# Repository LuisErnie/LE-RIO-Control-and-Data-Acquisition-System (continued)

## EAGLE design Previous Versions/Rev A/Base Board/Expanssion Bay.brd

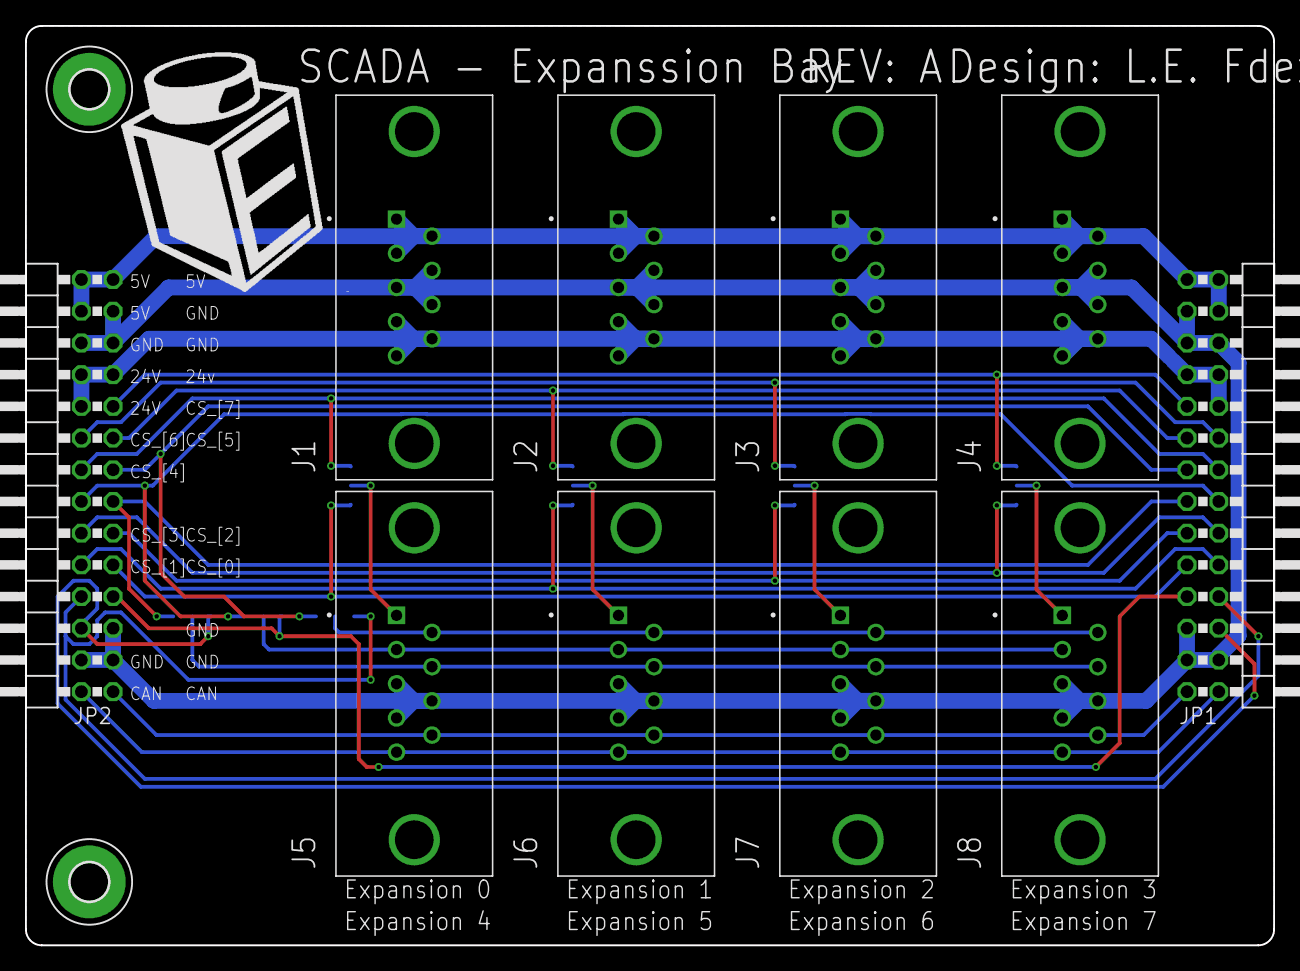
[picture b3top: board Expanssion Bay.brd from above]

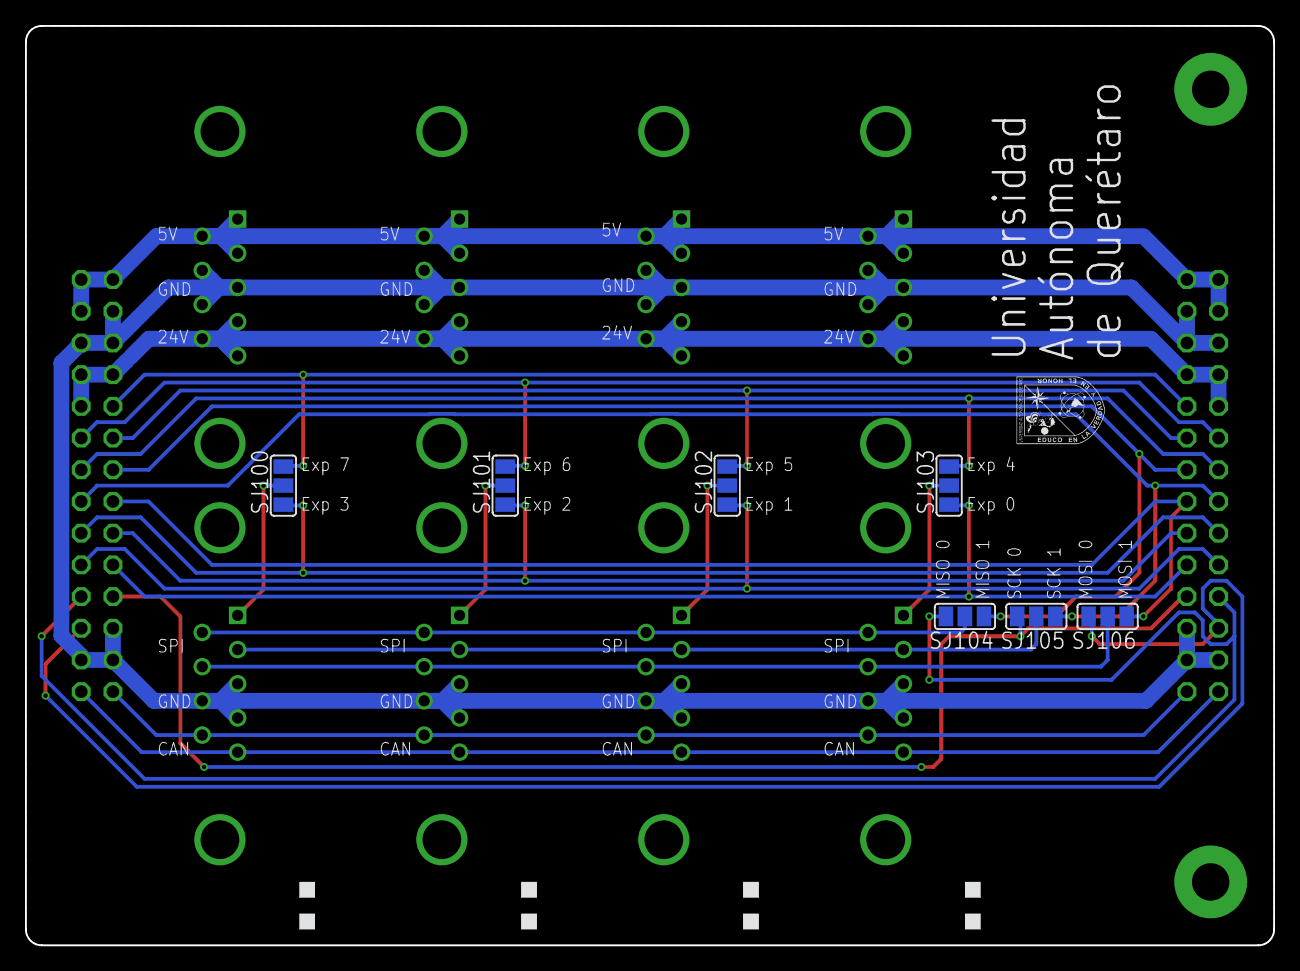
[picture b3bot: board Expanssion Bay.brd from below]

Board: 2 copper layers, 100.0 x 73.7 mm, 19 parts (7 on the bottom side), 26 nets.

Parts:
H1, H2: MOUNT-PAD-ROUND3.0; 3,0-PAD
J1, J2, J3, J4, J5, J6, J7, J8: LD09S24A4GV00LF
JP1, JP2: 2X14/90
SJ100, SJ101, SJ102, SJ103, SJ104, SJ105, SJ106: SJ_2

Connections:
+24V: J1.4, J1.5, J1.9, J2.4, J2.5, J2.9, J3.4, J3.5, J3.9, J4.4, J4.5, J4.9, JP1.7, JP1.8, JP1.10, JP2.20, JP2.21, JP2.22
AGND: J1.3, J1.7, J1.8, J2.3, J2.7, J2.8, J3.3, J3.7, J3.8, J4.3, J4.7, J4.8, J5.3, J5.4, J5.8, J6.3, J6.4, J6.8, J7.3, J7.4, J7.8, J8.3, J8.4, J8.8, JP1.3, JP1.5, JP1.6, JP1.23, JP1.25, JP1.26, JP2.3, JP2.4, JP2.5, JP2.23, JP2.24, JP2.25
CAN_H: J5.5, J6.5, J7.5, J8.5, JP1.28, JP2.2
CAN_L: J5.9, J6.9, J7.9, J8.9, JP1.27, JP2.1
CS_0: JP1.19, JP2.9, SJ103.1
CS_1: JP1.20, JP2.10, SJ102.1
CS_2: JP1.17, JP2.11, SJ101.1
CS_3: JP1.18, JP2.12, SJ100.1
CS_4: JP1.14, JP2.16, SJ103.3
CS_5: JP1.11, JP2.17, SJ102.3
CS_6: JP1.12, JP2.18, SJ101.3
CS_7: JP1.9, JP2.19, SJ100.3
CS_A: J5.1, SJ103.2
CS_B: J6.1, SJ102.2
CS_C: J7.1, SJ101.2
CS_D: J8.1, SJ100.2
MISO: J5.6, J6.6, J7.6, J8.6, SJ104.2
MISO_0: JP1.22, JP2.8, SJ104.1
MISO_1: JP1.13, JP2.15, SJ104.3
MOSI: J5.7, J6.7, J7.7, J8.7, SJ106.2
MOSI_0: JP1.24, JP2.6, SJ106.1
MOSI_1: JP1.15, JP2.13, SJ106.3
SCK: J5.2, J6.2, J7.2, J8.2, SJ105.2
SCK_0: JP1.21, JP2.7, SJ105.1
SCK_1: JP1.16, JP2.14, SJ105.3
VCCA: J1.1, J1.2, J1.6, J2.1, J2.2, J2.6, J3.1, J3.2, J3.6, J4.1, J4.2, J4.6, JP1.1, JP1.2, JP1.4, JP2.26, JP2.27, JP2.28

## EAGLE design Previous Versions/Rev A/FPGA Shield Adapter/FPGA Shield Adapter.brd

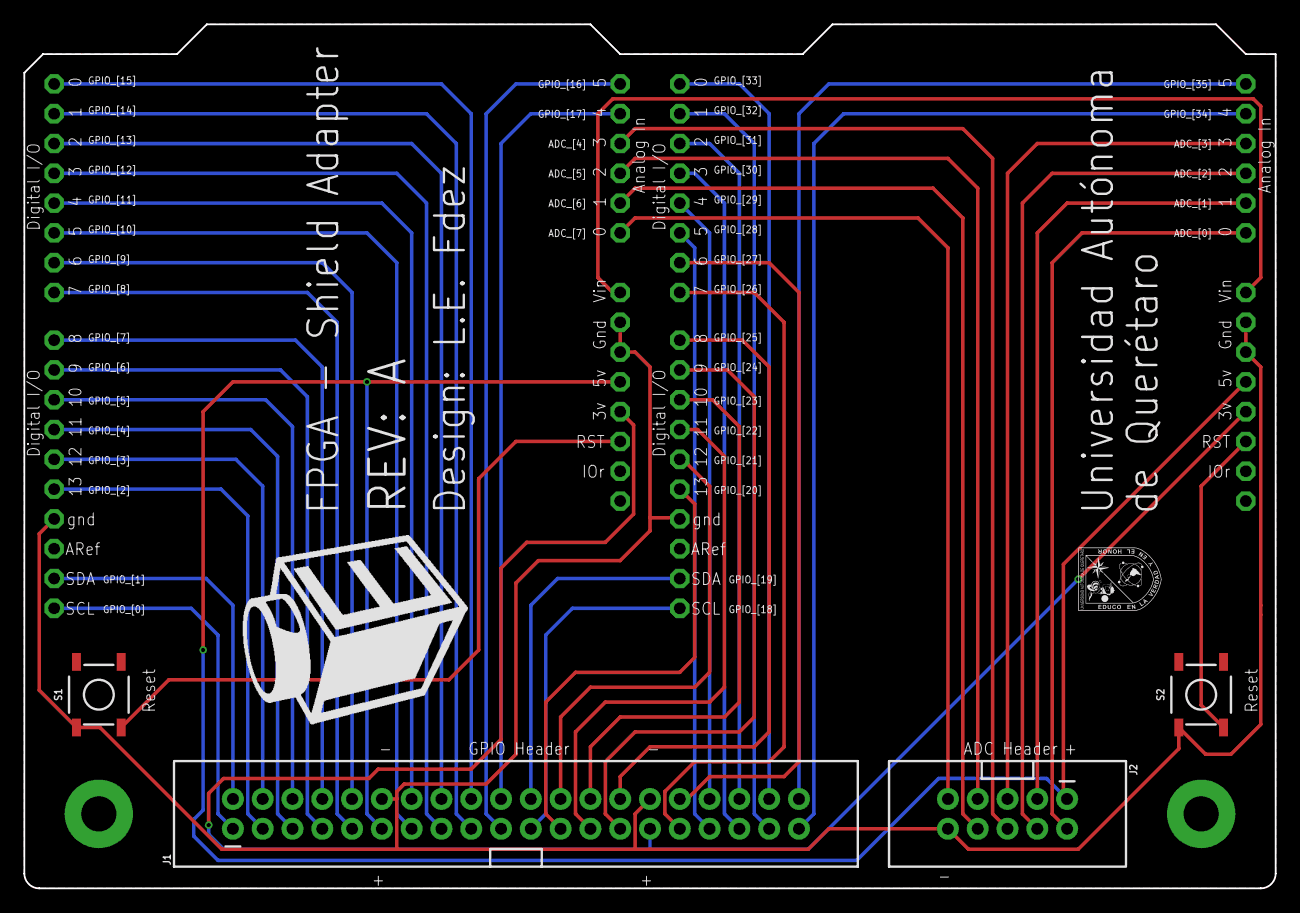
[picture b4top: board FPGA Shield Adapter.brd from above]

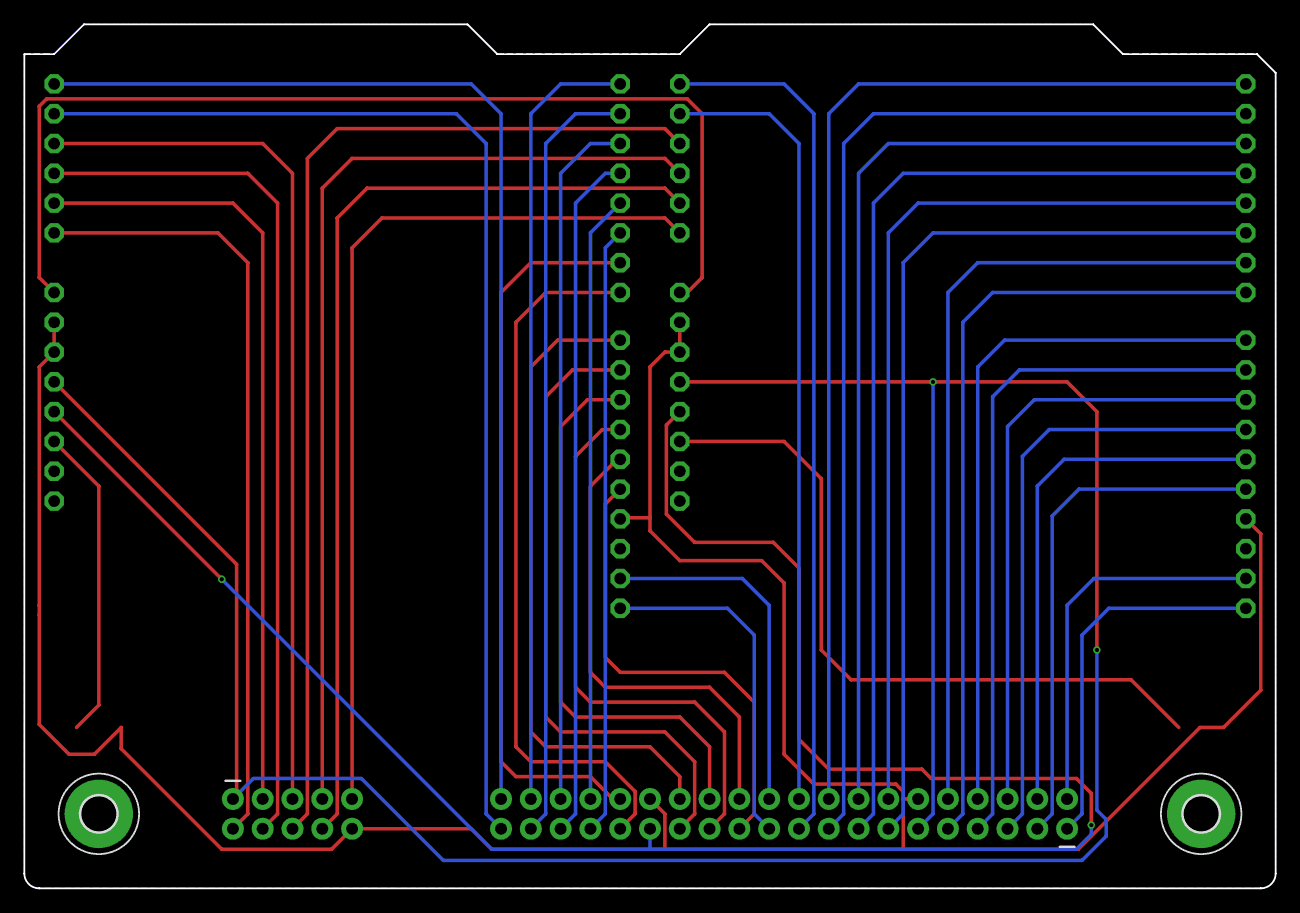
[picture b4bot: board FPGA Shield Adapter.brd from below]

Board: 2 copper layers, 106.7 x 73.7 mm, 8 parts (2 on the bottom side), 50 nets.

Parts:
H100, H101: MOUNT-PAD-ROUND3.0; 3,0-PAD
J1: CONN_20X2SHROUDED; 2X20_SHROUDED
J2: 2X5-SHROUDED
S1, S2: MOMENTARY-SWITCH-SPST-SMD-5.2MM; TACTILE_SWITCH_SMD_5.2MM
U1, U2: ARDUINOR3NODIM; ARDUINOR3-NODIM

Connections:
3.3V: J1.29, U1.3V, U2.3V
5V: J1.11, J2.1, U1.5V, U2.5V
ADC_0: J2.2, U2.A0
ADC_1: J2.3, U2.A1
ADC_2: J2.4, U2.A2
ADC_3: J2.5, U2.A3
ADC_4: J2.6, U1.A3
ADC_5: J2.7, U1.A2
ADC_6: J2.8, U1.A1
ADC_7: J2.9, U1.A0
D0: J1.40, U2.A5
D1: J1.39, U2.A4
D2: J1.38, U2.D0
D3: J1.37, U2.D1
D4: J1.36, U2.D2
D5: J1.35, U2.D3
D6: J1.34, U2.D4
D7: J1.33, U2.D5
D8: J1.32, U2.D6
D9: J1.31, U2.D7
D10: J1.28, U2.D8
D11: J1.27, U2.D9
D12: J1.26, U2.D10
D13: J1.25, U2.D11
D14: J1.24, U2.D12
D15: J1.23, U2.D13
D16: J1.22, U2.SDA
D17: J1.21, U2.SCL
D18: J1.20, U1.A4
D19: J1.19, U1.A5
D20: J1.18, U1.D0
D21: J1.17, U1.D1
D22: J1.16, U1.D2
D23: J1.15, U1.D3
D24: J1.14, U1.D4
D25: J1.13, U1.D5
D26: J1.10, U1.D6
D27: J1.9, U1.D7
D28: J1.8, U1.D8
D29: J1.7, U1.D9
D30: J1.6, U1.D10
D31: J1.5, U1.D11
D32: J1.4, U1.D12
D33: J1.3, U1.D13
D34: J1.2, U1.SDA
D35: J1.1, U1.SCL
GND: J1.12, J1.30, J2.10, S1.1, S2.1, U1.GND, U1.GND1, U1.GND2, U2.GND, U2.GND1, U2.GND2
unnamed: S2.3, U2.RESET
unnamed: S1.3, U1.RESET
VIN: U1.VIN, U2.VIN

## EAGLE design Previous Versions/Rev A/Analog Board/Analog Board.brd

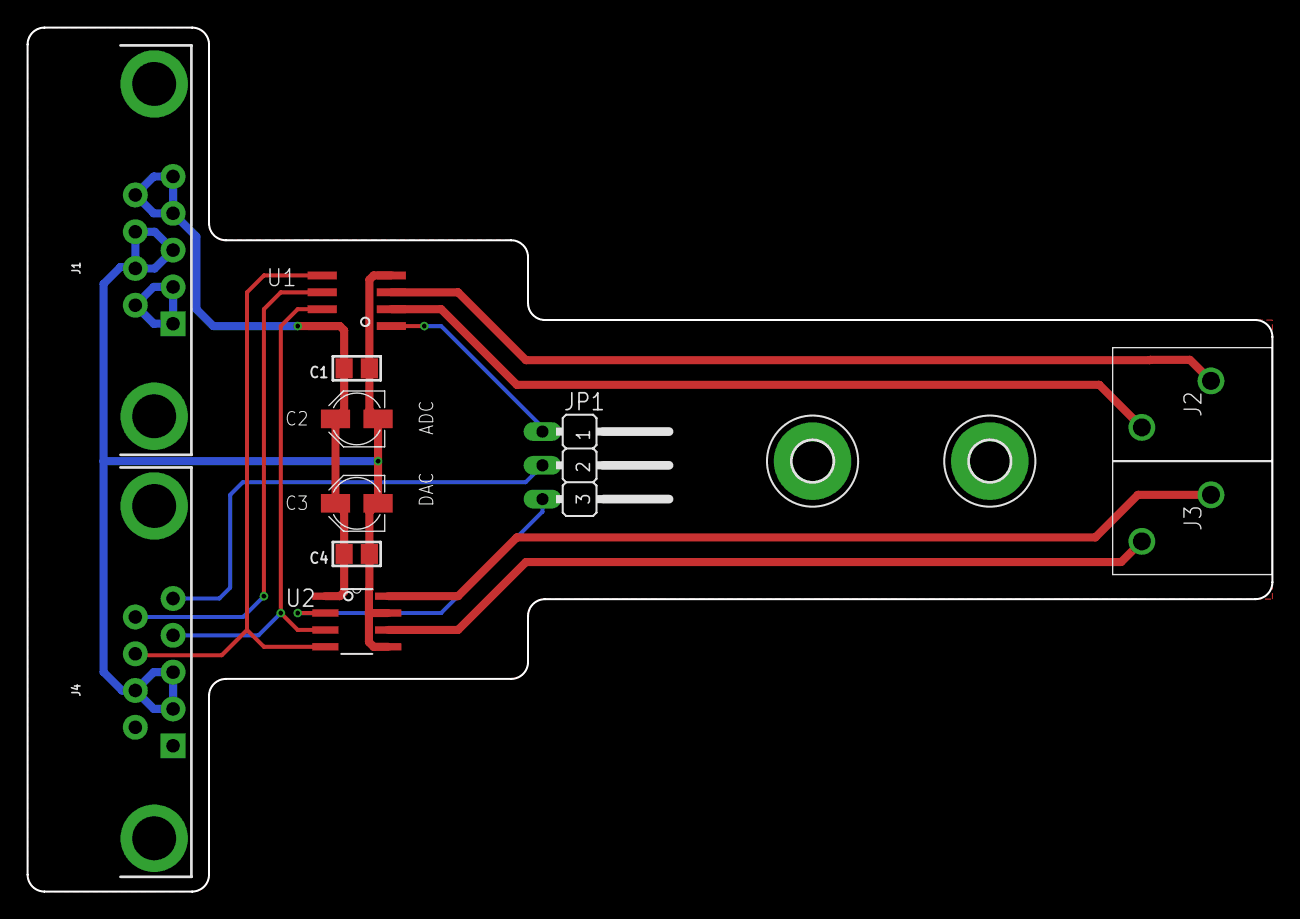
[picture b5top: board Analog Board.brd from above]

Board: 2 copper layers, 93.7 x 65.0 mm, 13 parts (0 on the bottom side), 13 nets.

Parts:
C1, C4: 0.1uF; 0805_NOTHERMALS
C2, C3: 1uF; PANASONIC_B
H1, H2: MOUNT-PAD-ROUND3.0; 3,0-PAD
J1, J4: DB9
J2, J3: 1-2834011-2; 128340112
JP1: JP2W
U1: MCP3202SN; SO-08
U2: MCP4822-E/SN; SOIC8-N_MC

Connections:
+24V: J1.1, J1.2, J1.6
AGND: C1.1, C2.-, C3.-, C4.1, J1.3, J1.7, J1.8, J4.2, J4.3, J4.7, U1.4, U2.5, U2.7
CS: J4.5, JP1.2
MISO: J4.9, U1.6
MOSI: J4.8, U1.5, U2.4
unnamed: JP1.3, U2.2
unnamed: JP1.1, U1.1
unnamed: J3.2, U2.8
unnamed: J3.1, U2.6
unnamed: J2.1, U1.2
unnamed: J2.2, U1.3
SCK: J4.4, U1.7, U2.3
VCCA: C1.2, C2.+, C3.+, C4.2, J1.4, J1.5, J1.9, U1.8, U2.1

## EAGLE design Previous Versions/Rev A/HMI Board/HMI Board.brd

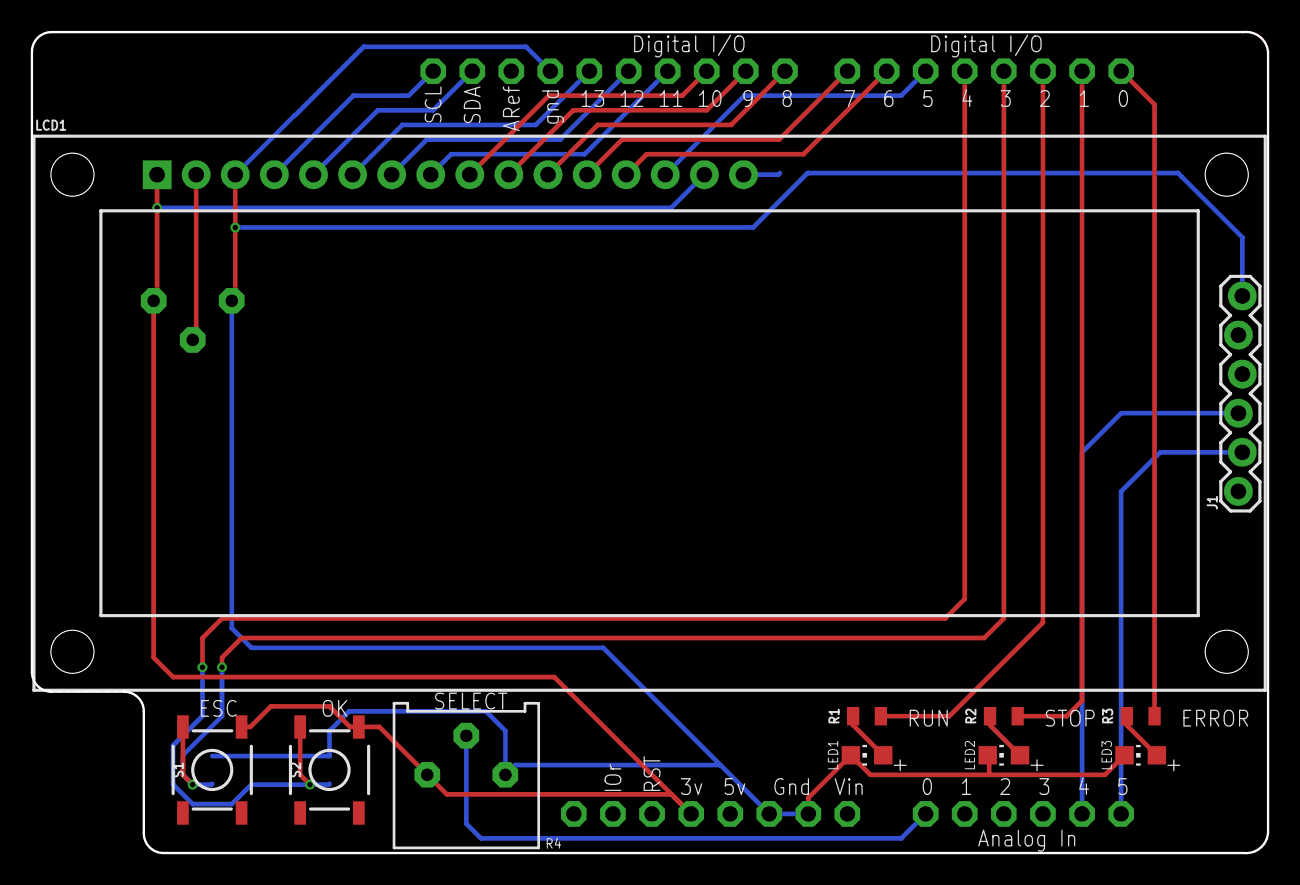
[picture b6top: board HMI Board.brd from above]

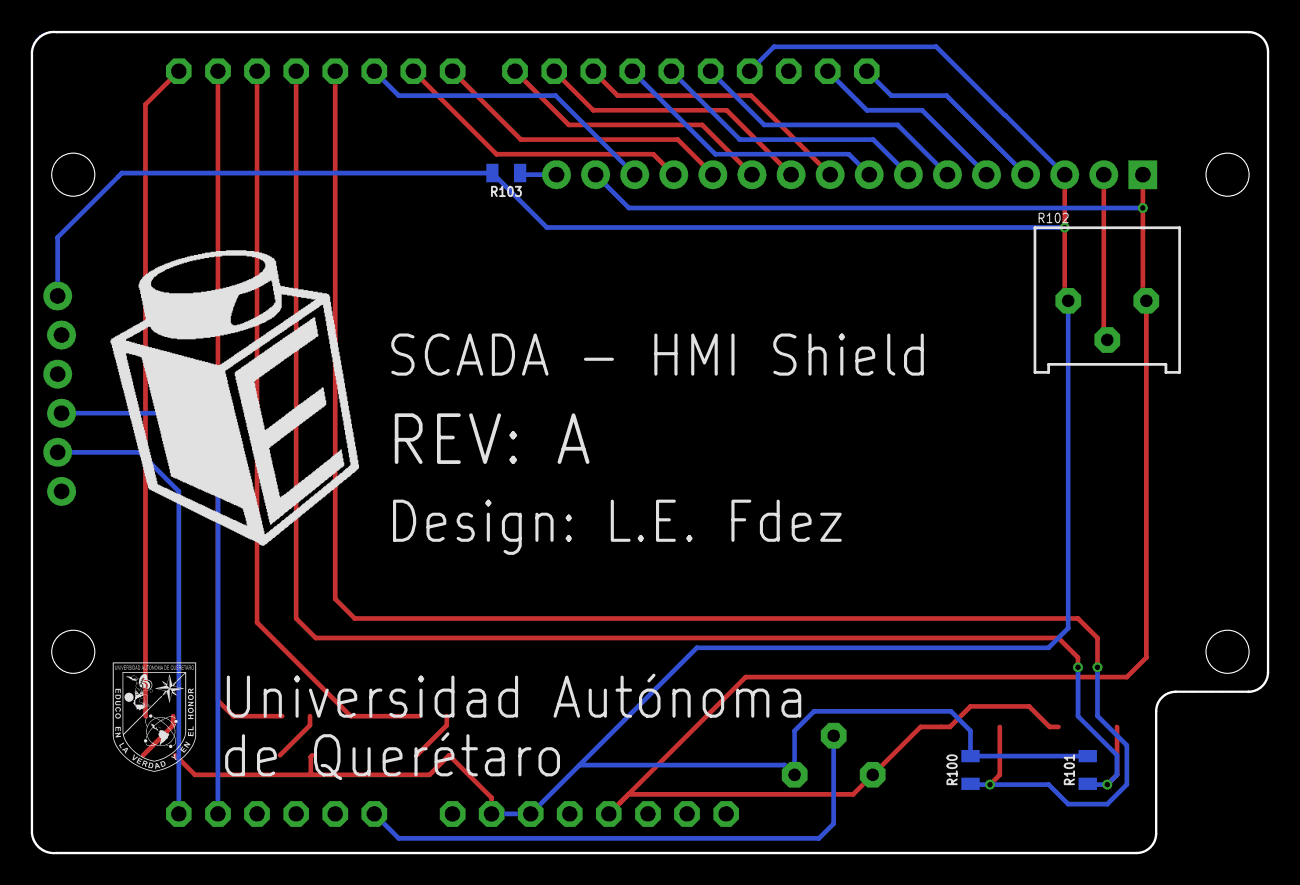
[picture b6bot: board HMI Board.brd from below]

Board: 2 copper layers, 80.3 x 53.4 mm, 16 parts (4 on the bottom side), 26 nets.

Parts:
J1: 1X06_LOCK
LCD1: LCD-16X2SILK; LCD-16X2
LED1, LED2, LED3: CHIP-LED0805
R1, R2, R3: 100E; 0805
R4, R102: 3386P
R100, R101, R103: 1k; 0805
S1, S2: MOMENTARY-SWITCH-SPST-SMD-5.2MM; TACTILE_SWITCH_SMD_5.2MM
U1: ARDUINOR3NODIM; ARDUINOR3-NODIM

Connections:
GND: J1.6, LCD1.3, LED1.C, LED2.C, LED3.C, R4.1, R100.2, R101.2, R102.1, R103.2, U1.GND, U1.GND1, U1.GND2
unnamed: LCD1.14, U1.D5
unnamed: LCD1.13, U1.D6
unnamed: LCD1.12, U1.D7
unnamed: LCD1.11, U1.D8
unnamed: LCD1.10, U1.D9
unnamed: LCD1.9, U1.D10
unnamed: LCD1.8, U1.D11
unnamed: LCD1.7, U1.D12
unnamed: R1.2, U1.D2
unnamed: LCD1.5, U1.SDA
unnamed: LCD1.4, U1.SCL
unnamed: R4.2, U1.A0
unnamed: LED1.A, R1.1
unnamed: J1.3, U1.A4
unnamed: J1.2, U1.A5
unnamed: LED2.A, R2.1
unnamed: LED3.A, R3.1
unnamed: LCD1.2, R102.2
unnamed: LCD1.16, R103.1
unnamed: LCD1.6, U1.D13
unnamed: R100.1, S2.3, U1.D4
unnamed: R101.1, S1.3, U1.D3
unnamed: R3.2, U1.D0
unnamed: R2.2, U1.D1
VCC: LCD1.1, LCD1.15, R4.3, R102.3, S1.1, S2.1, U1.3V

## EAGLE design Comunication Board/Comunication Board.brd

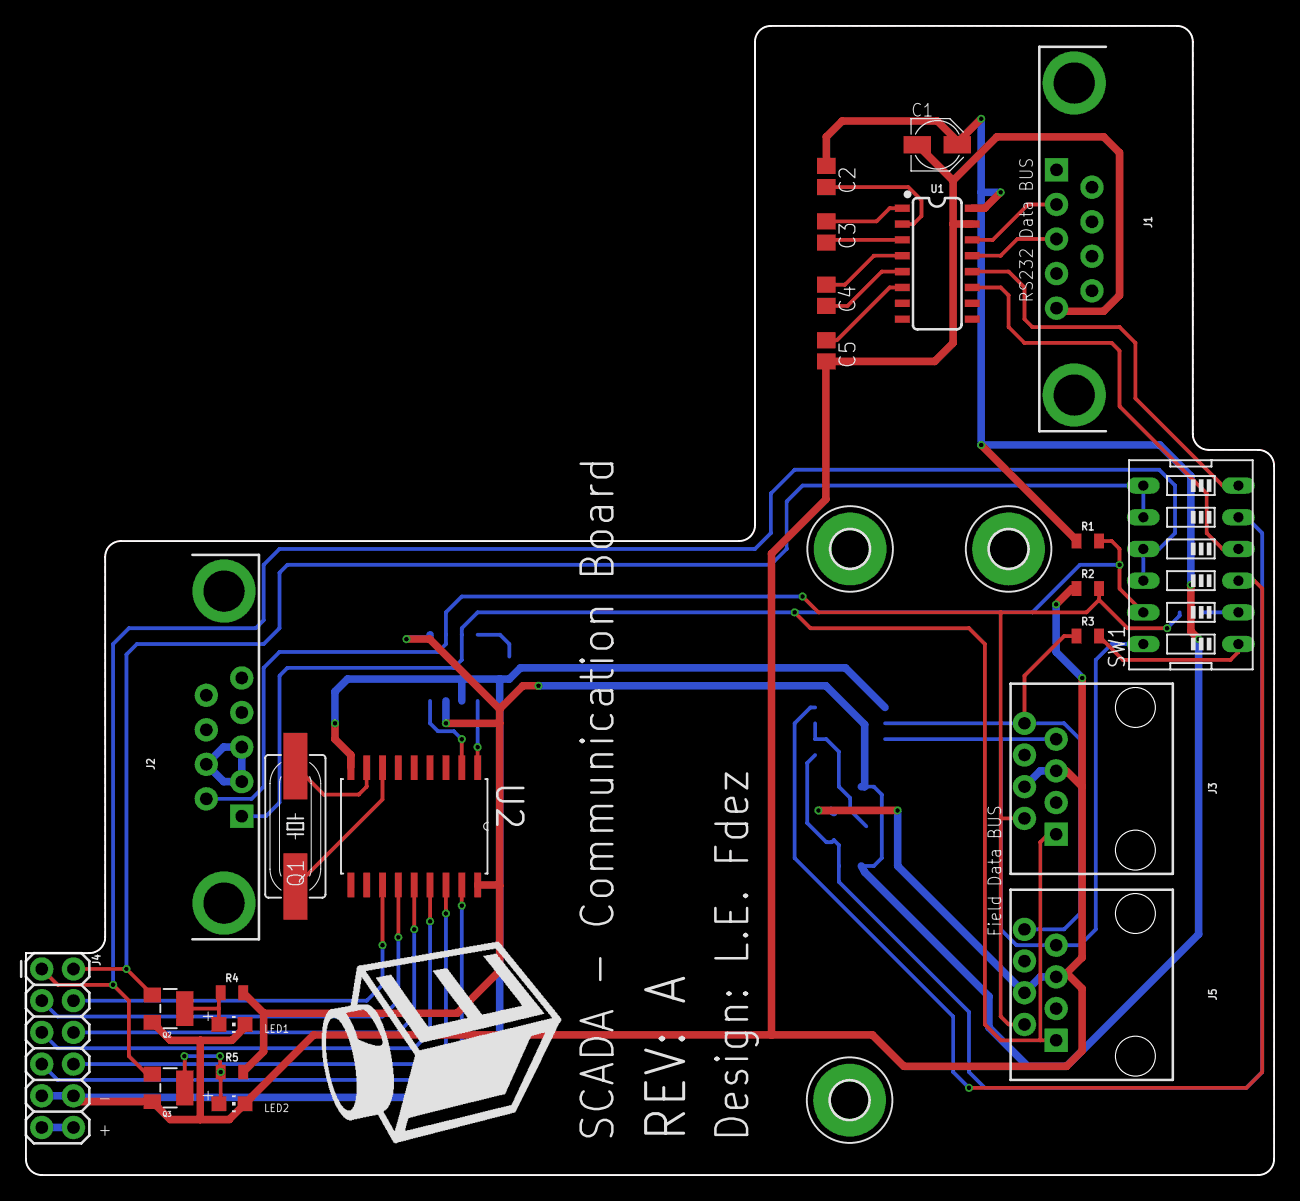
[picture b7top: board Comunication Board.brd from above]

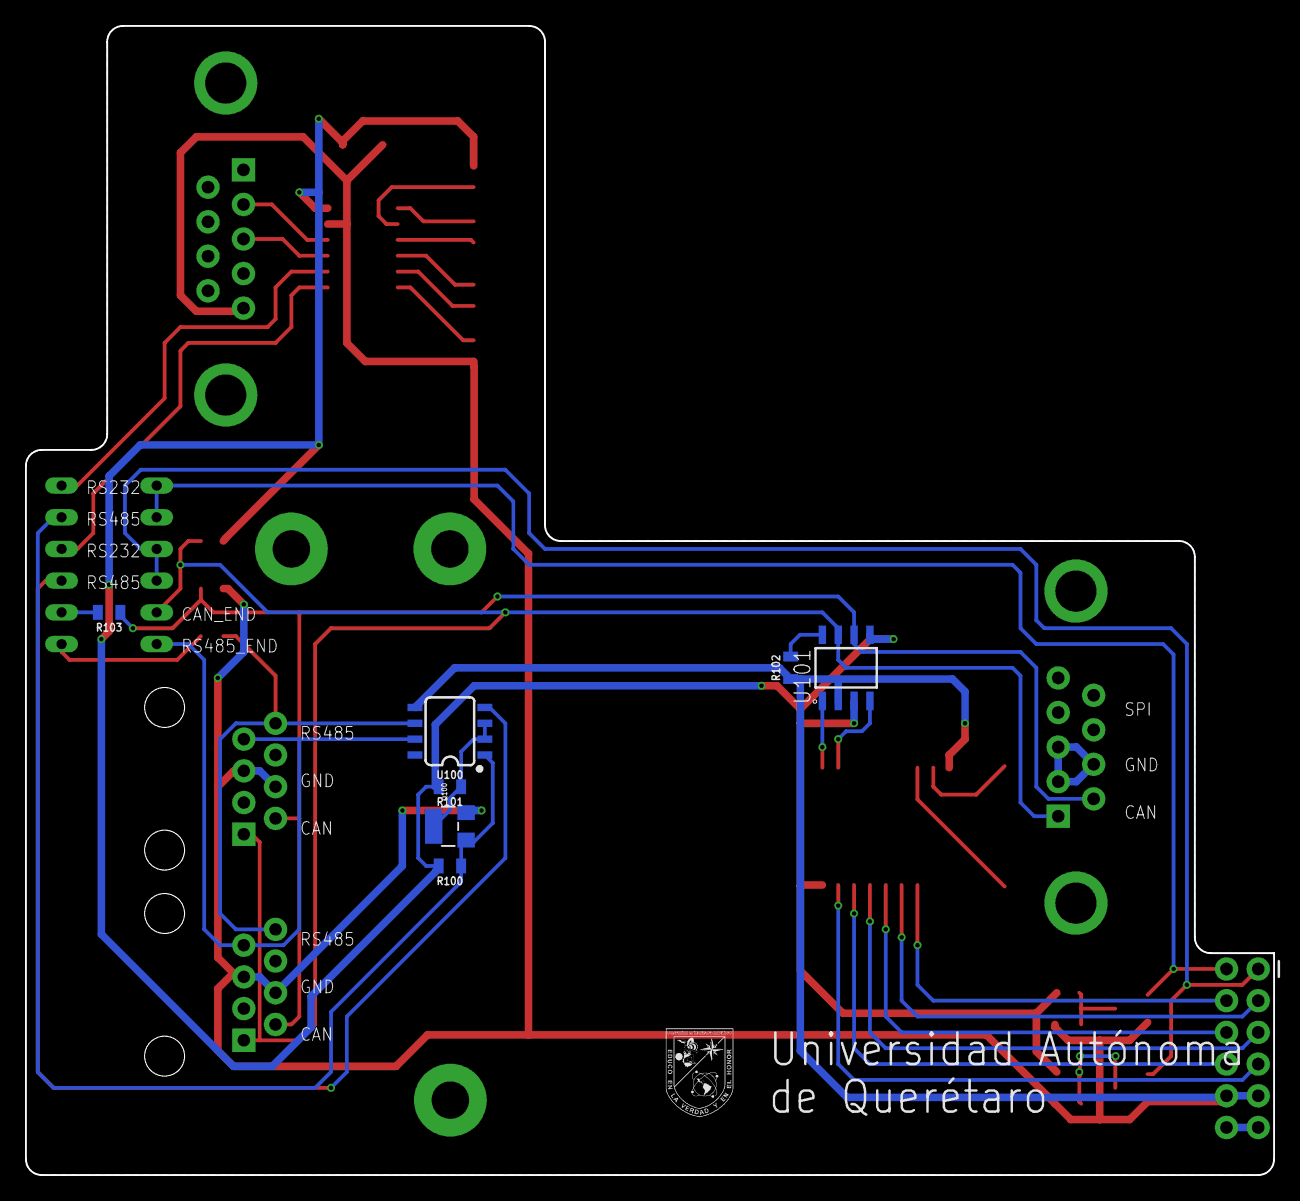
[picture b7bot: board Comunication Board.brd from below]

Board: 2 copper layers, 100.0 x 92.1 mm, 33 parts (7 on the bottom side), 38 nets.

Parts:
C1: 1uF; PANASONIC_B
C2, C3, C4, C5: 1uF; C0805
H1, H2, H3: MOUNT-PAD-ROUND3.0; 3,0-PAD
J1, J2: DB9
J3, J5: RJ45; RJ45-8
J4: 2X6 FEMALE; 2X6
LED1, LED2: CHIP-LED0805
Q1: 16MHz; HC49UP
Q2, Q3, Q100: SOT23-W
R1, R2, R4, R5: 1k; 0805
R3: 120E; 0805
R100, R101: 10k; 0805
R102: 100k; 0805
R103: 270E; 0805
SW1: EDG-06
U1: MAX3232; SO16
U2: MCP2515-I/SO; SOIC127P1034X264-18N
U100: MAX3485CSA; SO08
U101: MCP2562T-H/SN; SOIC127P600X175-8N

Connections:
3.3V: C1.+, C2.2, R1.2, R4.2, R5.2, R100.2, R101.2, U1.16, U2.18, U101.3, U101.5
232_RX: SW1.4, U1.11
232_TX: SW1.6, U1.12
485_RX: SW1.3, U100.4
485_TX: Q100.1, R100.1, SW1.5, U100.1
A: J3.8, J5.8, R3.1, U100.6
AGND: J2.2, J2.3, J2.7
B: J3.7, J5.7, SW1.12, U100.7
CAN_CS: J4.8, U2.16
CAN_H: J2.1, J3.1, J5.1, R1.1, SW1.11, U101.7
CAN_INT: J4.4, U2.12
CAN_L: J2.6, J3.2, J5.2, R2.2, R103.1, U101.6
CAN_MISO: J4.5, U2.15
CAN_MOSI: J4.6, U2.14
CAN_RESET: J4.7, U2.17
CAN_SCK: J4.3, U2.13
GND: C1.-, C5.2, J1.5, J3.4, J3.5, J4.9, J4.10, J5.4, J5.5, LED1.C, LED2.C, Q2.2, Q3.2, Q100.2, R2.1, R102.1, U1.15, U2.9, U100.5, U101.2
unnamed: C3.2, U1.3
unnamed: C2.1, U1.2
unnamed: C3.1, U1.1
unnamed: C4.1, U1.4
unnamed: C4.2, U1.5
unnamed: C5.1, U1.6
unnamed: R103.2, SW1.2
unnamed: LED2.A, Q3.3, R5.1
unnamed: J1.2, U1.14
unnamed: J1.3, U1.13
unnamed: LED1.A, Q2.3, R4.1
unnamed: U2.1, U101.1
unnamed: U2.2, U101.4
unnamed: Q1.2, U2.8
unnamed: R3.2, SW1.1
unnamed: Q1.1, U2.7
unnamed: Q100.3, R101.1, U100.2, U100.3
unnamed: R102.2, U101.8
RX: J4.1, Q3.1, SW1.9, SW1.10
TX: J4.2, Q2.1, SW1.7, SW1.8
VCC: J4.11, J4.12

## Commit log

2019-10-19 REV A
2020-01-19 Editing description
2021-05-13 Updated for Rev D
    Files for Rev D Added along with Datasheets and Documentation
2021-05-21 Update LICENSE.md
    Licence Change
